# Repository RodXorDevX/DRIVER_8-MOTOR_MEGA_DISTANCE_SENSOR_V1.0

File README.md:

# DRIVER_8-MOTOR_MEGA_DISTANCE_SENSOR_V1.0

## Descripción

Este proyecto consiste en el diseño de una placa electrónica (PCB) para el control de hasta 8 motores y la integración de sensores de distancia, ideal para aplicaciones de robótica, automatización y sistemas embebidos. El diseño está basado en el microcontrolador ATMEGA2560, ampliamente utilizado en plataformas como Arduino MEGA, lo que facilita la programación y expansión del sistema.

La placa permite el uso de módulos para motores paso a paso como el Pololu A4988 o similares, y la conexión de sensores ultrasónicos para la detección de presencia o distancia.

## Aplicación artística

Esta placa fue utilizada en un proyecto de arte donde un cuadro contenía una figura de un anciano en bronce, cuyas partes se desarmaban automáticamente al detectar la presencia de una persona frente al cuadro mediante un sensor ultrasónico. Cuando no se detectaba presencia, el cuadro se rearmaba. También era posible invertir el comportamiento: el cuadro se reordenaba cuando había presencia.

## Características principales

- **Control de 8 motores:** Permite manejar hasta 8 motores de manera independiente mediante módulos A4988 o compatibles.
- **Sensores de distancia:** Integración sencilla de sensores ultrasónicos para medición de distancias o detección de presencia.
- **Microcontrolador ATMEGA2560:** 256 KB de memoria Flash, 8 KB de SRAM, 4 KB de EEPROM, 86 pines de I/O, 16 canales ADC de 10 bits, 12 canales PWM de 16 bits, 4 puertos USART.
- **Conectores estándar:** Pines y headers compatibles con módulos y shields comunes.
- **Archivos Gerber incluidos:** Listos para fabricación profesional de la PCB.

## Archivos incluidos

- `DRIVER_8 MOTOR_MEGA_DISTANCE_SENSOR_V1.0.sch`: Esquemático del circuito.
- `DRIVER_8 MOTOR_MEGA_DISTANCE_SENSOR_V1.0.brd`: Diseño de la PCB.
- Archivos Gerber (`.GBL`, `.GTL`, `.GBO`, `.GTO`, etc.): Para fabricación de la placa.
- `Board.png`: Imagen de la PCB.
- `Schematic.png`: Imagen del esquemático.
- `.TXT`, `.gpi`: Archivos de taladros y detalles de fabricación.

## Uso

1. **Revisión del diseño:** Consulta las imágenes incluidas para visualizar el esquemático y la PCB.
2. **Fabricación:** Utiliza los archivos Gerber para mandar a fabricar la placa en cualquier servicio profesional.
3. **Montaje:** Ensambla los componentes siguiendo el esquemático. Instala los módulos A4988 o similares en los zócalos correspondientes y conecta el sensor ultrasónico en el header designado.
4. **Programación:** Utiliza el entorno de Arduino o AVR para cargar el firmware al ATMEGA2560.

## Créditos

- Diseño original por Rodrigo Urquieta.
- Basado en el microcontrolador ATMEGA2560.

---

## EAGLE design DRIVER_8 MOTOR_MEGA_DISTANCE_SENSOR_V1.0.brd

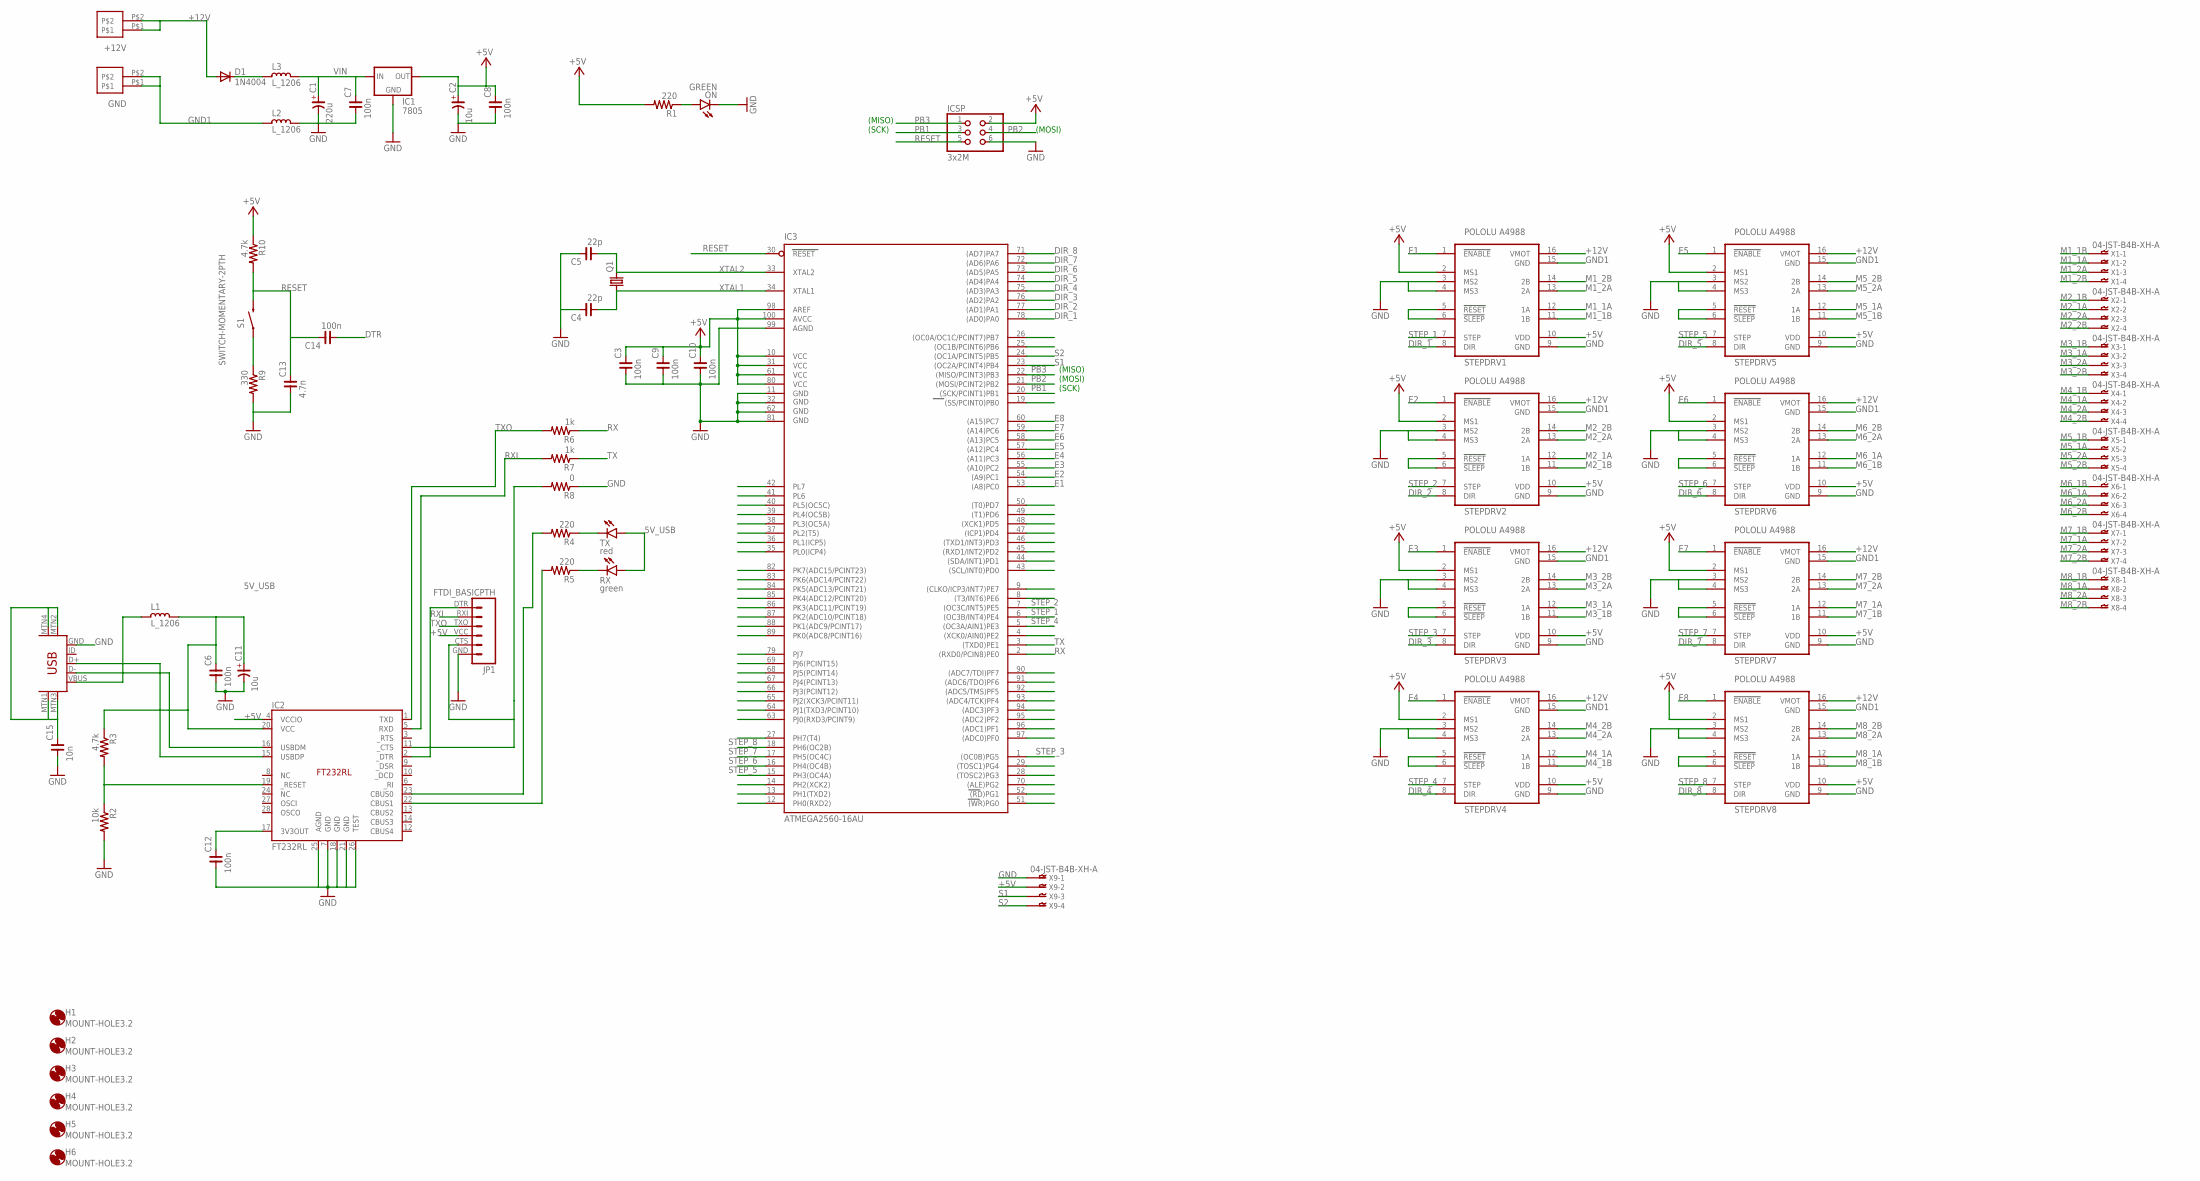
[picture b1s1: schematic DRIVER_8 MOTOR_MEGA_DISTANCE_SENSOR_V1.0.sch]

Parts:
+12V: SCREW_T_10MM
C1: 220u; CE-050X100
C2: 10u; CE-050X100
C3, C6, C7, C8, C9, C10, C12, C14: 100n; C050-075X030
C4, C5: 22p; C050-075X030
C11: 10u; CE-025X060
C13: 4.7n; C050-075X030
C15: 10n; C050-075X030
D1: 1N4004; DO41-10
GND: SCREW_T_10MM
H1, H2, H3, H4, H5, H6: MOUNT-HOLE3.2; 3,2
IC1: 7805; TO-220-ALT
IC2: FT232RL; SSOP-28
IC3: ATMEGA2560-16AU; TQFP100
ICSP: 3x2M; 2X03
JP1: FTDI_BASICPTH; FTDI_BASIC
L1, L2, L3: L_1206; L1206
ON: GREEN; LED3MM
Q1: CRYSTALHC49S; HC49/S
R1, R4, R5: 220; 0805
R2: 10k; 0805
R3, R10: 4.7k; 0805
R6, R7: 1k; 0805
R8: 0; 0805
R9: 330; 0805
RX: green; LED3MM
S1: SWITCH-MOMENTARY-2PTH; TACTILE-PTH
STEPDRV1, STEPDRV2, STEPDRV3, STEPDRV4, STEPDRV5, STEPDRV6, STEPDRV7, STEPDRV8: POLOLU A4988; POLOLULU2128
TX: red; LED3MM
U$1: USB-MINIB-5PIN; USB-MINIB
X1, X2, X3, X4, X5, X6, X7, X8, X9: 04-JST-B4B-XH-A; B4B-XH

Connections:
5V_USB: C6.2, C11.+, IC2.20 (VCC), L1.1, R3.1, RX.A, TX.A
+5V: C2.+, C3.2, C8.2, C9.2, C10.2, IC1.OUT, IC2.4 (VCCIO), IC3.10 (VCC), IC3.31 (VCC1), IC3.61 (VCC2), IC3.80 (VCC3), IC3.98 (AREF), IC3.100 (AVCC), ICSP.2, JP1.VCC (4), R1.2, R10.1, STEPDRV1.2 (MS1), STEPDRV1.10 (VDD), STEPDRV2.2 (MS1), STEPDRV2.10 (VDD), STEPDRV3.2 (MS1), STEPDRV3.10 (VDD), STEPDRV4.2 (MS1), STEPDRV4.10 (VDD), STEPDRV5.2 (MS1), STEPDRV5.10 (VDD), STEPDRV6.2 (MS1), STEPDRV6.10 (VDD), STEPDRV7.2 (MS1), STEPDRV7.10 (VDD), STEPDRV8.2 (MS1), STEPDRV8.10 (VDD), X9.P$2
+12V: +12V.P$1, +12V.P$2, D1.A, STEPDRV1.16 (VMOT), STEPDRV2.16 (VMOT), STEPDRV3.16 (VMOT), STEPDRV4.16 (VMOT), STEPDRV5.16 (VMOT), STEPDRV6.16 (VMOT), STEPDRV7.16 (VMOT), STEPDRV8.16 (VMOT)
DIR_1: IC3.78 ((AD0)PA0), STEPDRV1.8 (DIR)
DIR_2: IC3.77 ((AD1)PA1), STEPDRV2.8 (DIR)
DIR_3: IC3.76 ((AD2)PA2), STEPDRV3.8 (DIR)
DIR_4: IC3.75 ((AD3)PA3), STEPDRV4.8 (DIR)
DIR_5: IC3.74 ((AD4)PA4), STEPDRV5.8 (DIR)
DIR_6: IC3.73 ((AD5)PA5), STEPDRV6.8 (DIR)
DIR_7: IC3.72 ((AD6)PA6), STEPDRV7.8 (DIR)
DIR_8: IC3.71 ((AD7)PA7), STEPDRV8.8 (DIR)
DTR: C14.1, IC2.2 (_DTR), JP1.DTR (1)
E1: IC3.53 ((A8)PC0), STEPDRV1.1 (!ENABLE)
E2: IC3.54 ((A9)PC1), STEPDRV2.1 (!ENABLE)
E3: IC3.55 ((A10)PC2), STEPDRV3.1 (!ENABLE)
E4: IC3.56 ((A11)PC3), STEPDRV4.1 (!ENABLE)
E5: IC3.57 ((A12)PC4), STEPDRV5.1 (!ENABLE)
E6: IC3.58 ((A13)PC5), STEPDRV6.1 (!ENABLE)
E7: IC3.59 ((A14)PC6), STEPDRV7.1 (!ENABLE)
E8: IC3.60 ((A15)PC7), STEPDRV8.1 (!ENABLE)
GND: C1.-, C2.-, C3.1, C4.2, C5.2, C6.1, C7.1, C8.1, C9.1, C10.1, C11.-, C12.1, C13.1, C15.1, IC1.GND, IC2.7 (GND), IC2.18 (GND), IC2.21 (GND), IC2.25 (AGND), IC2.26 (TEST), IC3.11 (GND), IC3.32 (GND1), IC3.62 (GND2), IC3.81 (GND3), IC3.99 (AGND), ICSP.6, JP1.GND (6), L2.1, ON.K (C), R2.2, R8.1, R9.2, STEPDRV1.3 (MS2), STEPDRV1.4 (MS3), STEPDRV1.9 (GND), STEPDRV2.3 (MS2), STEPDRV2.4 (MS3), STEPDRV2.9 (GND), STEPDRV3.3 (MS2), STEPDRV3.4 (MS3), STEPDRV3.9 (GND), STEPDRV4.3 (MS2), STEPDRV4.4 (MS3), STEPDRV4.9 (GND), STEPDRV5.3 (MS2), STEPDRV5.4 (MS3), STEPDRV5.9 (GND), STEPDRV6.3 (MS2), STEPDRV6.4 (MS3), STEPDRV6.9 (GND), STEPDRV7.3 (MS2), STEPDRV7.4 (MS3), STEPDRV7.9 (GND), STEPDRV8.3 (MS2), STEPDRV8.4 (MS3), STEPDRV8.9 (GND), U$1.GND, X9.P$1
GND1: GND.P$1, GND.P$2, L2.2, STEPDRV1.15 (GND), STEPDRV2.15 (GND), STEPDRV3.15 (GND), STEPDRV4.15 (GND), STEPDRV5.15 (GND), STEPDRV6.15 (GND), STEPDRV7.15 (GND), STEPDRV8.15 (GND)
M1_1A: STEPDRV1.12 (1A), X1.P$2
M1_1B: STEPDRV1.11 (1B), X1.P$1
M1_2A: STEPDRV1.13 (2A), X1.P$3
M1_2B: STEPDRV1.14 (2B), X1.P$4
M2_1A: STEPDRV2.12 (1A), X2.P$2
M2_1B: STEPDRV2.11 (1B), X2.P$1
M2_2A: STEPDRV2.13 (2A), X2.P$3
M2_2B: STEPDRV2.14 (2B), X2.P$4
M3_1A: STEPDRV3.12 (1A), X3.P$2
M3_1B: STEPDRV3.11 (1B), X3.P$1
M3_2A: STEPDRV3.13 (2A), X3.P$3
M3_2B: STEPDRV3.14 (2B), X3.P$4
M4_1A: STEPDRV4.12 (1A), X4.P$2
M4_1B: STEPDRV4.11 (1B), X4.P$1
M4_2A: STEPDRV4.13 (2A), X4.P$3
M4_2B: STEPDRV4.14 (2B), X4.P$4
M5_1A: STEPDRV5.12 (1A), X5.P$2
M5_1B: STEPDRV5.11 (1B), X5.P$1
M5_2A: STEPDRV5.13 (2A), X5.P$3
M5_2B: STEPDRV5.14 (2B), X5.P$4
M6_1A: STEPDRV6.12 (1A), X6.P$2
M6_1B: STEPDRV6.11 (1B), X6.P$1
M6_2A: STEPDRV6.13 (2A), X6.P$3
M6_2B: STEPDRV6.14 (2B), X6.P$4
M7_1A: STEPDRV7.12 (1A), X7.P$2
M7_1B: STEPDRV7.11 (1B), X7.P$1
M7_2A: STEPDRV7.13 (2A), X7.P$3
M7_2B: STEPDRV7.14 (2B), X7.P$4
M8_1A: STEPDRV8.12 (1A), X8.P$2
M8_1B: STEPDRV8.11 (1B), X8.P$1
M8_2A: STEPDRV8.13 (2A), X8.P$3
M8_2B: STEPDRV8.14 (2B), X8.P$4
unnamed: L1.2, U$1.VBUS
unnamed: IC2.16 (USBDM), U$1.D-
unnamed: ON.A, R1.1
unnamed: STEPDRV2.5 (!RESET), STEPDRV2.6 (!SLEEP)
unnamed: STEPDRV3.5 (!RESET), STEPDRV3.6 (!SLEEP)
unnamed: IC2.15 (USBDP), U$1.D+
unnamed: STEPDRV1.5 (!RESET), STEPDRV1.6 (!SLEEP)
unnamed: STEPDRV4.5 (!RESET), STEPDRV4.6 (!SLEEP)
unnamed: STEPDRV5.5 (!RESET), STEPDRV5.6 (!SLEEP)
unnamed: STEPDRV6.5 (!RESET), STEPDRV6.6 (!SLEEP)
unnamed: STEPDRV7.5 (!RESET), STEPDRV7.6 (!SLEEP)
unnamed: STEPDRV8.5 (!RESET), STEPDRV8.6 (!SLEEP)
unnamed: C12.2, IC2.17 (3V3OUT)
unnamed: D1.C, L3.2
unnamed: R4.1, TX.K (C)
unnamed: R5.1, RX.K (C)
unnamed: C15.2, U$1.MTN1 (MTN2), U$1.MTN2 (MTN3), U$1.MTN3 (MTN1), U$1.MTN4
unnamed: IC2.23 (CBUS0), R4.2
unnamed: IC2.22 (CBUS1), R5.2
unnamed: IC2.11 (_CTS), JP1.CTS (5), R8.2
unnamed: R9.1, S1.1
unnamed: IC2.19 (_RESET), R2.1, R3.2
PB0: IC3.19 ((SS/PCINT0)PB0)
PB1: IC3.20 ((SCK/PCINT1)PB1), ICSP.3
PB2: IC3.21 ((MOSI/PCINT2)PB2), ICSP.4
PB3: IC3.22 ((MISO/PCINT3)PB3), ICSP.1
PB6: IC3.25 ((OC1B/PCINT6)PB6)
PB7: IC3.26 ((OC0A/OC1C/PCINT7)PB7)
PD7: IC3.50 ((T0)PD7)
PG0: IC3.51 ((WR)PG0)
PG1: IC3.52 ((RD)PG1)
PG2: IC3.70 ((ALE)PG2)
PL0: IC3.35 (PL0(ICP4))
PL1: IC3.36 (PL1(ICP5))
PL2: IC3.37 (PL2(T5))
PL3: IC3.38 (PL3(OC5A))
PL4: IC3.39 (PL4(OC5B))
PL5: IC3.40 (PL5(OC5C))
PL6: IC3.41 (PL6)
PL7: IC3.42 (PL7)
RESET: C13.2, C14.2, IC3.30 (RESET), ICSP.5, R10.2, S1.3 (2)
RX: IC3.2 ((RXD0/PCIN8)PE0), R6.1
RXD2: IC3.12 (PH0(RXD2))
RXD3: IC3.63 (PJ0(RXD3/PCINT9))
RXI: IC2.5 (RXD), JP1.RXI (2), R7.2
S1: IC3.23 ((OC2A/PCINT4)PB4), X9.P$3
S2: IC3.24 ((OC1A/PCINT5)PB5), X9.P$4
STEP_1: IC3.6 ((OC3B/INT4)PE4), STEPDRV1.7 (STEP)
STEP_2: IC3.7 ((OC3C/INT5)PE5), STEPDRV2.7 (STEP)
STEP_3: IC3.1 ((OC0B)PG5), STEPDRV3.7 (STEP)
STEP_4: IC3.5 ((OC3A/AIN1)PE3), STEPDRV4.7 (STEP)
STEP_5: IC3.15 (PH3(OC4A)), STEPDRV5.7 (STEP)
STEP_6: IC3.16 (PH4(OC4B)), STEPDRV6.7 (STEP)
STEP_7: IC3.17 (PH5(OC4C)), STEPDRV7.7 (STEP)
STEP_8: IC3.18 (PH6(OC2B)), STEPDRV8.7 (STEP)
TX: IC3.3 ((TXD0)PE1), R7.1
TXD2: IC3.13 (PH1(TXD2))
TXD3: IC3.64 (PJ1(TXD3/PCINT10))
TXO: IC2.1 (TXD), JP1.TXO (3), R6.2
VIN: C1.+, C7.2, IC1.IN, L3.1
XTAL1: C4.1, IC3.34 (XTAL1), Q1.1
XTAL2: C5.1, IC3.33 (XTAL2), Q1.2

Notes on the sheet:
(SCK)
(MISO)
(MOSI)

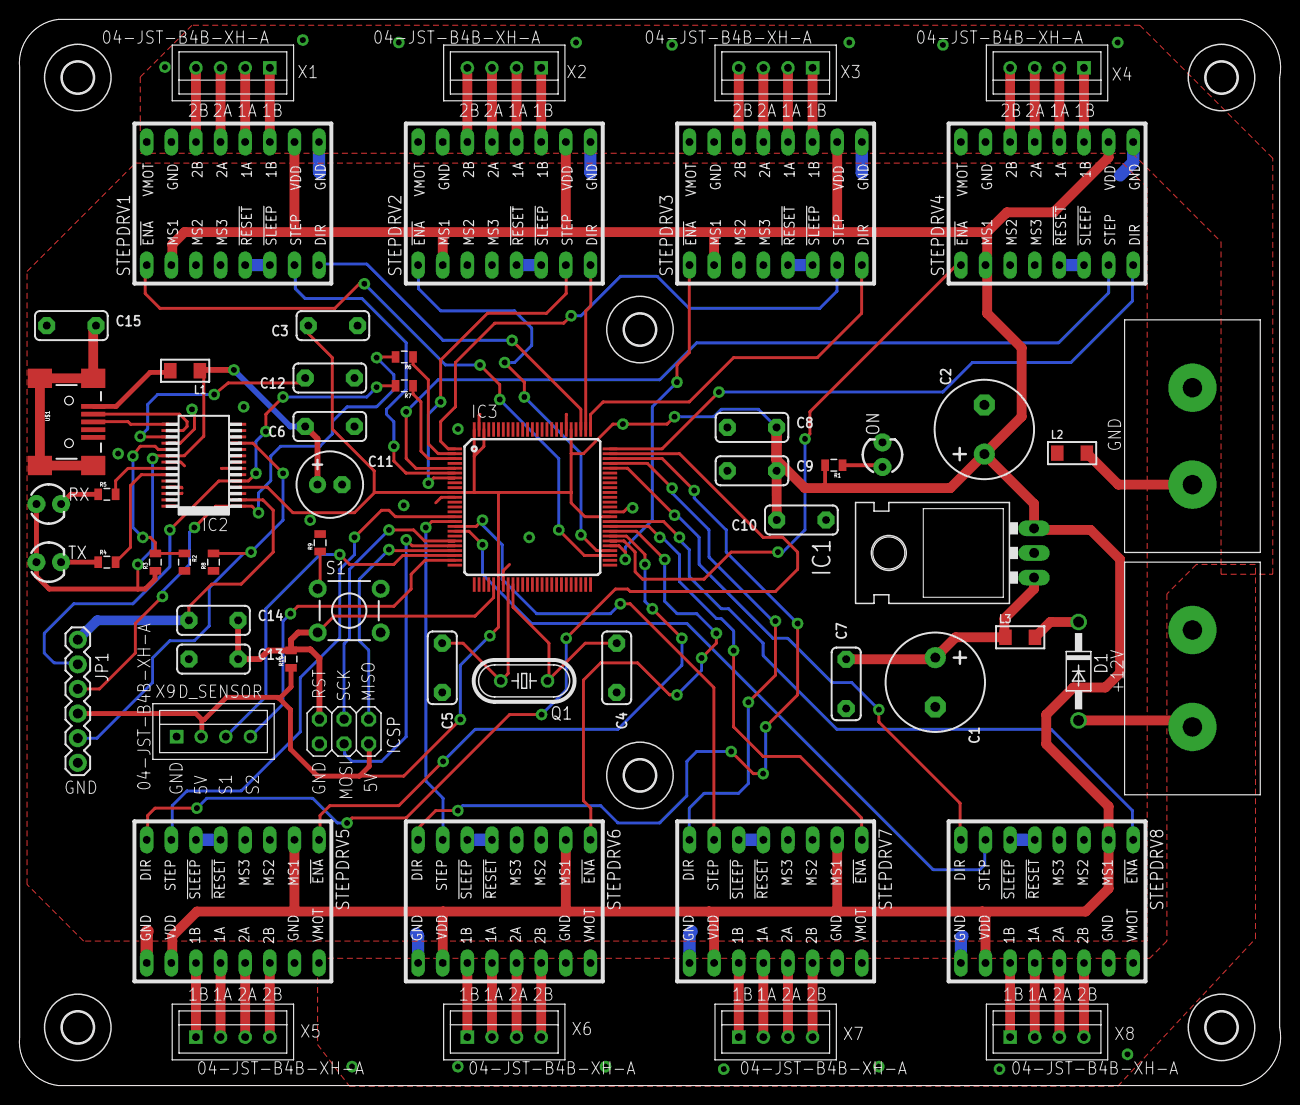
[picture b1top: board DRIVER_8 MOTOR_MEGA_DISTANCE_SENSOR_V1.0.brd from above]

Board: 2 copper layers, 130.1 x 110.0 mm, 65 parts (0 on the bottom side), 97 nets.

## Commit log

2025-06-28 Upload
2025-07-02 Actualizacion de Readme

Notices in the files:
parts and their libraries:
rc-master: Copyright (C) 2007, Bob Starr
SparkFun-PowerIC: Licensing: Creative Commons ShareAlike 4.0 International - https://creativecommons.org/licenses/by-sa/4.0
